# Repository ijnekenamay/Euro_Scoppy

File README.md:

# Euro_Scoppy
Project to make an Eurorack version of "([Scoppy](https://play.google.com/store/apps/details?id=xyz.fhdm.scoppy&hl=ja&gl=US))" oscilloscope that works with Raspberry pi pico and Android phone.

!!!!!!! note !!!!!!!!
- I had long forgotten about this project. I finished the test build and verified that it works fine, but then I remembered I needed another oscilloscope for calibration and threw it away. Nothing wrong with just looking at the waveform shape. Enjoy.
- Be sure to use a cable with “OTG” function. This is also shown in the Scoppy reference.
- Payment for the "Scoppy" application is required to use the two channels.
- This project is ongoing.

## Now progress

- [x] Idea sketch
- [x] Draw proto Schematics
- [x] Design proto PCB
- [x] Proto type
- [x] Design PCB
- [x] Fabrication PCB
- [x] Test Build

## Latest Status

## Feature

- Two channels of input are available.
- AC/DC coupling can be selected for each input.
- ±30V and ±8V can be changed.
- It is based on an analog front-end PCB designed by [picoLABO](https://picolabo.org/plu2212-dso/)).

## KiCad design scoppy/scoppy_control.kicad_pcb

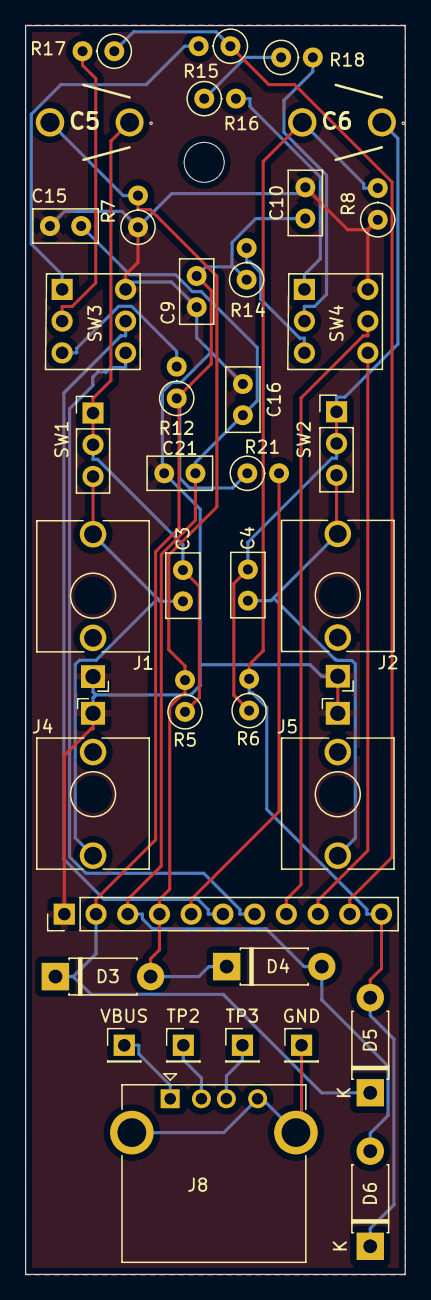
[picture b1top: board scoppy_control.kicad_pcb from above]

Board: 2 copper layers, 30.4 x 100.0 mm, 39 parts (0 on the bottom side), 26 nets.

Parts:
C3, C4, C9, C10, C15, C16: 0.1uF; C_Disc_D5.0mm_W2.5mm_P2.50mm
C5, C6: 30pF; TZ03_B_
C21: 10uF; C_Disc_D5.0mm_W2.5mm_P2.50mm
D3, D4, D5, D6: D_Schottky; D_DO-41_SOD81_P7.62mm_Horizontal
GND: GND; PinHeader_1x01_P2.54mm_Vertical
J1: CH1; Jack_3.5mm_QingPu_WQP-PJ398SM_Vertical_CircularHoles
J2: CH2; Jack_3.5mm_QingPu_WQP-PJ398SM_Vertical_CircularHoles
J4: CH1_Through; Jack_3.5mm_QingPu_WQP-PJ398SM_Vertical_CircularHoles
J5: CH2_Through; Jack_3.5mm_QingPu_WQP-PJ398SM_Vertical_CircularHoles
J8: USB_A; USB_A_CONNFLY_DS1095-WNR0
R5, R6: 1M; R_Axial_DIN0207_L6.3mm_D2.5mm_P2.54mm_Vertical
R7, R8: 100k; R_Axial_DIN0207_L6.3mm_D2.5mm_P2.54mm_Vertical
R12, R14, R21: 15k; R_Axial_DIN0207_L6.3mm_D2.5mm_P2.54mm_Vertical
R15, R16: 180R; R_Axial_DIN0207_L6.3mm_D2.5mm_P2.54mm_Vertical
R17, R18: 1k; R_Axial_DIN0207_L6.3mm_D2.5mm_P2.54mm_Vertical
REF1: MountingHole_3.2mm_M3
REF5: PinHeader_1x11_P2.54mm_Vertical
SW1, SW2: AC/DCcoupling; PinHeader_1x03_P2.54mm_Vertical
SW3, SW4: Switch±30V/±8V/; toggle_dpdt_mod
TP2: TP2; PinHeader_1x01_P2.54mm_Vertical
TP3: TP3; PinHeader_1x01_P2.54mm_Vertical
VBUS: VBUS; PinHeader_1x01_P2.54mm_Vertical

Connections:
+3V3: C9.2, C10.2, D3.1 (K), D5.1 (K), R12.1, R14.1, R21.1, REF5.2
-3V3: C15.2, C16.2, C21.1, D4.2 (A), D6.2 (A), REF5.3
CH1: C3.1, J1.T, J4.T, SW1.3 (C)
CH2: C4.1, J2.T, J5.T, SW2.3 (C)
GND: C9.1, C10.1, C15.1, C16.1, C21.2, J1.S, J2.S, J4.S, J5.S, R7.1, R8.1, REF5.1, SW3.2 (B), SW4.2 (B)
GPIO2: REF5.6, SW3.4 (A)
GPIO3: REF5.7, SW3.6 (C)
GPIO4: REF5.8, SW4.4 (A)
GPIO5: REF5.9, SW4.6 (C)
unnamed: C3.2, C5.1, R5.1, SW1.1 (A), SW1.2 (B)
unnamed: C4.2, C6.1, R6.1, SW2.1 (A), SW2.2 (B)
unnamed: C5.2, D3.2 (A), D4.1 (K), R5.2, R7.2, REF5.4
unnamed: C6.2, D5.2 (A), D6.1 (K), R6.2, R8.2, REF5.11
unnamed: R21.2, REF5.5
unnamed: GND.1, J8.4 (GND), J8.5 (Shield)
unnamed: J8.1 (VBUS), VBUS.1
unnamed: J8.3 (D+), TP3.1
unnamed: J8.2 (D-), TP2.1
unnamed: R15.1, R17.1, REF5.10
unnamed: R12.2, SW3.5 (B)
unnamed: R16.1, R18.1
unnamed: R14.2, SW4.5 (B)
unnamed: R15.2, SW3.1 (A)
unnamed: R16.2, SW4.1 (A)
unnamed: R17.2, SW3.3 (C)
unnamed: R18.2, SW4.3 (C)

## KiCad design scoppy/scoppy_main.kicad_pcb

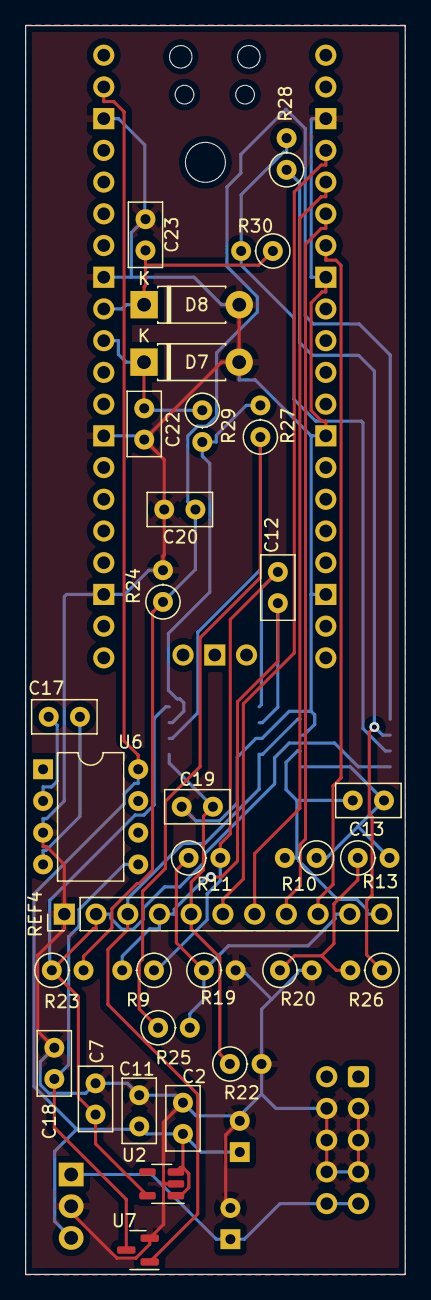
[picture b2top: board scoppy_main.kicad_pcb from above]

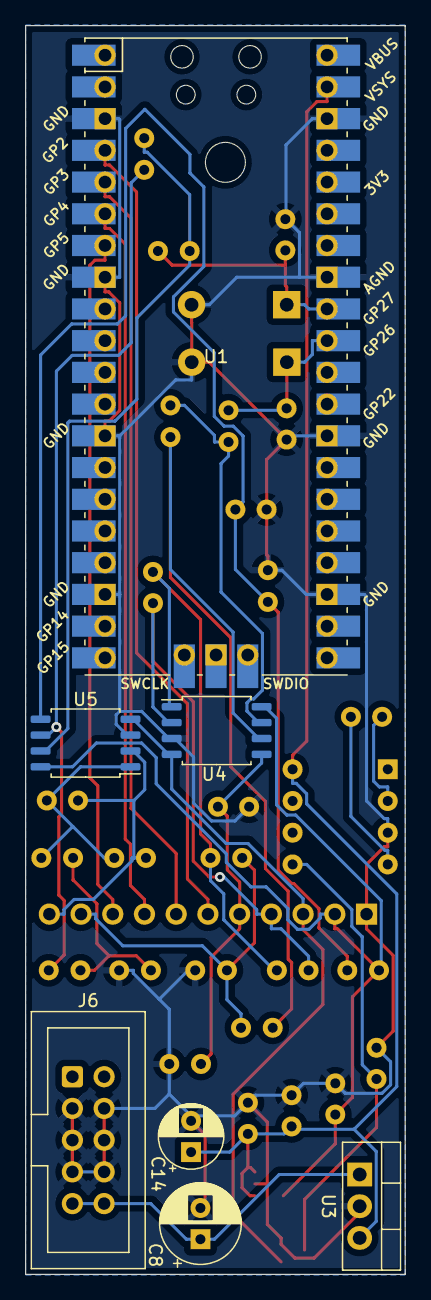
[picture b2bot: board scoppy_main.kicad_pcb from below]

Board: 2 copper layers, 30.4 x 100.0 mm, 40 parts (7 on the bottom side), 26 nets.

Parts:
C2, C7, C11, C17, C18: 10uF; C_Disc_D5.0mm_W2.5mm_P2.50mm
C8: 100uF; CP_Radial_D6.3mm_P2.50mm
C12, C13, C22, C23: 200p; C_Disc_D5.0mm_W2.5mm_P2.50mm
C14: 10uF; CP_Radial_D5.0mm_P2.50mm
C19, C20: 0.1uF; C_Disc_D5.0mm_W2.5mm_P2.50mm
D7, D8: D_Schottky; D_DO-41_SOD81_P7.62mm_Horizontal
J6: POWER; IDC-Header_2x05_P2.54mm_Vertical
R9, R10: 100k; R_Axial_DIN0207_L6.3mm_D2.5mm_P2.54mm_Vertical
R11, R13, R29, R30: 2.7k; R_Axial_DIN0207_L6.3mm_D2.5mm_P2.54mm_Vertical
R19, R20, R27, R28: 220k; R_Axial_DIN0207_L6.3mm_D2.5mm_P2.54mm_Vertical
R22, R24: 1k; R_Axial_DIN0207_L6.3mm_D2.5mm_P2.54mm_Vertical
R23: 15k; R_Axial_DIN0207_L6.3mm_D2.5mm_P2.54mm_Vertical
R25, R26: 30k; R_Axial_DIN0207_L6.3mm_D2.5mm_P2.54mm_Vertical
REF2: MountingHole_3.2mm_M3
REF4: PinHeader_1x11_P2.54mm_Vertical
U1: Pico; RPi_Pico_SMD_TH
U2: XC6201; SOT-23-5
U3: LM7805_TO220; TO-220-3_Vertical
U4, U5: NJM2746M; SOP-8_5.28x5.23mm_P1.27mm
U6: ICL7660; DIP-8_W7.62mm
U7: XC6902; SOT-23

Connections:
+3V3: C7.1, R23.1, REF4.2, U2.5 (VOUT), U4.8 (V+), U5.8 (V+)
+5V: C2.1, C11.1, C14.1, U1.39 (VSYS), U2.1 (VIN), U2.3 (CE), U3.3 (VO), U6.8 (V+)
+12V: C8.1, J6.9, J6.10, U3.1 (VI)
-3V3: REF4.3, U4.4 (V-), U5.4 (V-), U7.1 (VO)
-5V: C18.1, U6.5 (VOUT), U7.3 (VI)
ADC0: C22.2, D7.1 (K), R29.1, U1.31 (GPIO26_ADC0)
ADC1: C23.2, D8.1 (K), R30.1, U1.32 (GPIO27_ADC1)
GND: C2.2, C7.2, C8.2, C11.2, C14.2, C18.2, C19.1, C20.1, C22.1, C23.1, D7.2 (A), D8.2 (A), J6.3, J6.4, J6.5, J6.6, J6.7, J6.8, R19.2, R20.2, R22.2, R24.2, REF4.1, U1.3 (GND), U1.8 (GND), U1.13 (GND), U1.18 (GND), U1.23 (GND), U1.28 (GND), U1.33 (AGND), U1.38 (GND), U2.2 (GND), U3.2 (GND), U4.3 (+), U5.3 (+), U6.3 (GND), U7.2 (GND)
GPIO2: REF4.6, U1.4 (GPIO2)
GPIO3: REF4.7, U1.5 (GPIO3)
GPIO4: REF4.8, U1.6 (GPIO4)
GPIO5: REF4.9, U1.7 (GPIO5)
unnamed: C12.1, R9.2, REF4.4, U4.2 (-)
unnamed: C12.2, R9.1, R11.2, U4.1
unnamed: C13.1, R10.2, REF4.11, U5.2 (-)
unnamed: C13.2, R10.1, R13.2, U5.1
unnamed: C17.1, U6.2 (CAP+)
unnamed: C17.2, U6.4 (CAP-)
unnamed: C19.2, R22.1, REF4.5, U4.5 (+)
unnamed: C20.2, R23.2, R24.1, U5.5 (+)
unnamed: R11.1, R19.1, R25.2, REF4.10
unnamed: R13.1, R20.1, R26.2
unnamed: R25.1, R27.1, U4.6 (-)
unnamed: R26.1, R28.1, U5.6 (-)
unnamed: R27.2, R29.2, U4.7
unnamed: R28.2, R30.2, U5.7

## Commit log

2023-02-06 AddFIle
2023-02-06 Update README.md
    Add README
